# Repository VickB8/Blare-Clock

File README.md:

A Small custom desk clock powered by a XIAO ESP32-C3 with a color display and Wi-Fi time sync.

# Inspiration

I wanted to make a small desk clock that was more interesting than a normal digital clock I decided to design the PCB, Case and firmware myself use an ESP32-C3 so the clock could connect to Wifi and automatically keep the synchronisation.
I also wanted the final clock to look like an actual finished product instead of just a developement board connected to a display.

# How it Works

The clock uses a Seeed Studio XIAO ESP32-C3 as the main microcontroller. When it starts up, it connects to Wi-Fi and gets the current time using NTP.

The time is then displayed on the display.

The electronics are mounted inside a custom 3D-printed case that I designed specifically for the PCB and display.

# Challenges

One of the biggest challenges was getting the display and XIAO ESP32-C3 working together. I had to figure out the correct pins and how to control the display.

I also had some problems with the KiCad libraries and footprints for the XIAO ESP32-C3. Getting the PCB and its 3D models to show correctly took some troubleshooting.

Another challenge was designing the case. I originally made the display opening too small and didn't leave enough room for the display wires and USB connection. I had to go back and modify the case so the display could actually be connected and the USB port could be accessed.

# What I Learned

How to design a PCB in KiCad
How to work with custom footprints and libraries
How to use an ESP32-C3 with Wi-Fi
How NTP time synchronization works
How to design a 3D-printed enclosure around electronics
How to troubleshoot PCB and 3D-model issues

# Components 

Seeed Studio XIAO ESP32-C3
TFT display
Custom PCB
Connecting wires
3D-printed enclosure
MX style keyboard switches
white blank dsa caps
3.3v piezo buzzer
M3x5x4 heat inserts M3x8mm screws

# Software

Arduino IDE
ESP32 Arduino Core
Adafruit GFX Library
Adafruit ST7789 Library
SPI
WiFi
Time / NTP

# Features

Wi-Fi time synchronization
NTP-based accurate time
Color display

# Design Files

PCB

The PCB was designed in KiCad and contains the connections between the XIAO ESP32-C3 and the display.

Schematic

Case

The enclosure was designed to hold the electronics while leaving access for the display and USB port.

Firmware

The firmware is written in Arduino/C++ and handles Wi-Fi connection, NTP time synchronization, and drawing the clock interface on the display.

Final Result

This project helped me learn more about PCB design, embedded programming, displays, and designing physical enclosures for electronics. I started with the individual components and gradually worked toward making the complete clock.

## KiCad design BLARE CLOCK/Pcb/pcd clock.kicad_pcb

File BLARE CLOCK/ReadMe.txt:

# BLARE Clock

A custom digital clock built using a **Seeed Studio XIAO ESP32-C3**, **ST7789 TFT display**, custom PCB, and a 3D-printed enclosure.

## Project Overview

This project is a compact Wi-Fi-enabled digital clock. The ESP32-C3 connects to Wi-Fi and retrieves the current time using an NTP time server. The time and date are displayed on an ST7789 TFT screen.

## Features

* Wi-Fi connectivity
* Automatic time synchronization using NTP
* Digital time display
* Date display
* Custom PCB
* Custom 3D-printed enclosure
* ST7789 TFT display
* Seeed Studio XIAO ESP32-C3

## Hardware

| Component       | Description                |
| --------------- | -------------------------- |
| Microcontroller | Seeed Studio XIAO ESP32-C3 |
| Display         | ST7789 284 × 76 TFT        |
| PCB             | Custom-designed PCB        |
| Enclosure       | Custom 3D-printed case     |
| Firmware        | Arduino / ESP32            |
| Connectivity    | Wi-Fi                      |

## Firmware

The firmware is written using the Arduino IDE and runs on the XIAO ESP32-C3.

The firmware:

1. Initializes the ST7789 display.
2. Connects to Wi-Fi.
3. Synchronizes the clock using an NTP server.
4. Retrieves the local date and time.
5. Displays the time and date on the TFT.

### Libraries

* Adafruit GFX Library
* Adafruit ST7735 and ST7789 Library
* SPI
* WiFi
* ESP32 time functions

## Bill of Materials

| Component                   |                  Quantity |
| --------------------------- | ------------------------: |
| Seeed Studio XIAO ESP32-C3  |                         1 |
| ST7789 284 × 76 TFT Display |                         1 |
| Custom PCB                  |                         1 |
| 3D-printed enclosure        |                         1 |
| Other electronic components | As specified in schematic |

## Project Structure

```text
BLARE-Clock/
├── CAD/
│   └── Clock.step
│
├── PCB/
│   ├── clock.kicad_pro
│   ├── clock.kicad_sch
│   └── clock.kicad_pcb
│
├── Firmware/
│   └── clock.ino
│
├── Production/
│   ├── gerbers.zip
│   ├── Top.step
│   ├── Bottom.step
│
└── README.txt
```

## Tools Used

* KiCad — schematic and PCB design
* Arduino IDE — firmware development
* Blender / CAD software — enclosure design
* 3D printer — enclosure manufacturing

## Credits

This project was created as part of the **Hack Club BLARE** hardware project.

Built with:

* Seeed Studio XIAO ESP32-C3
* ST7789 TFT
* KiCad
* Arduino
* 3D printing

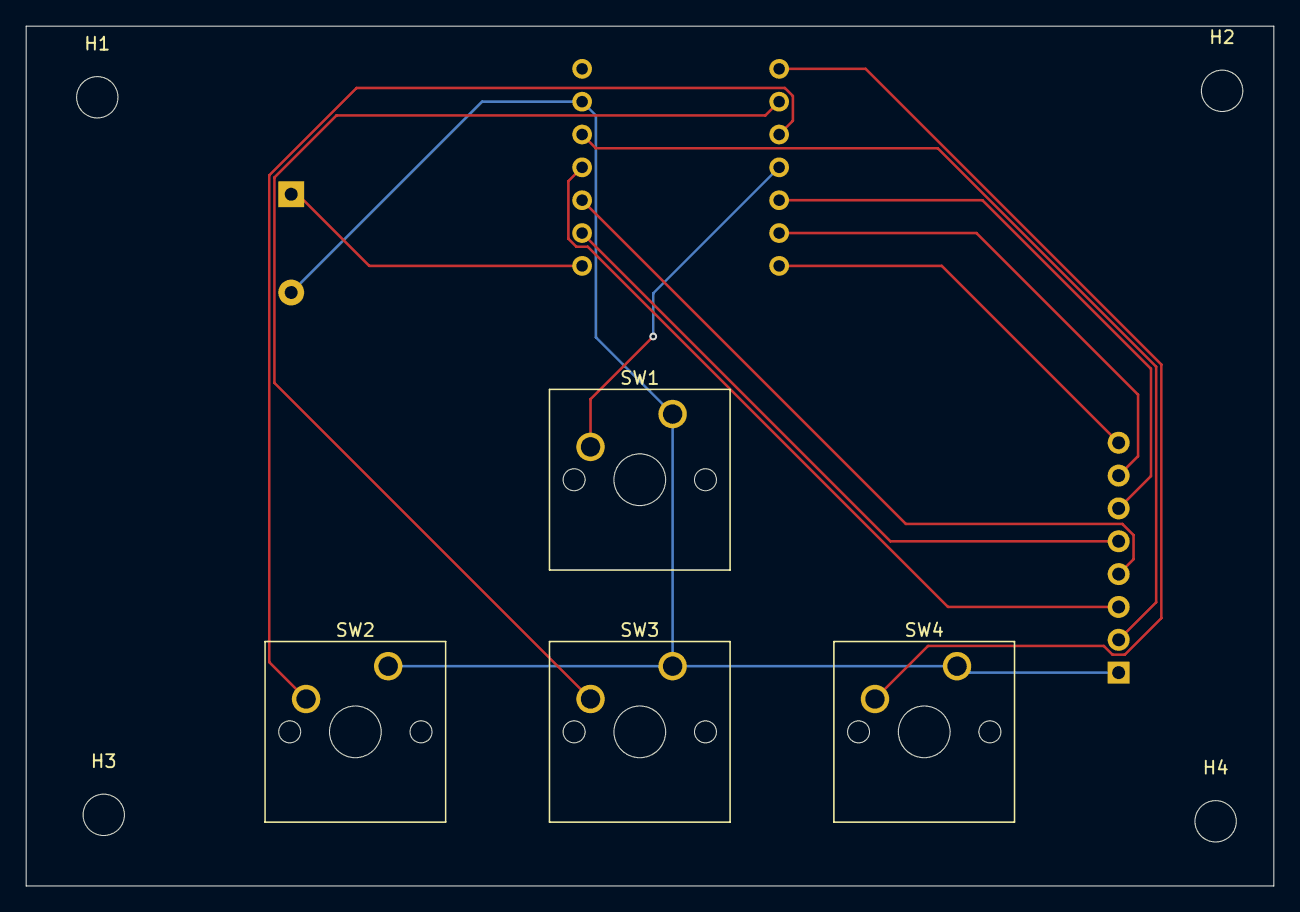
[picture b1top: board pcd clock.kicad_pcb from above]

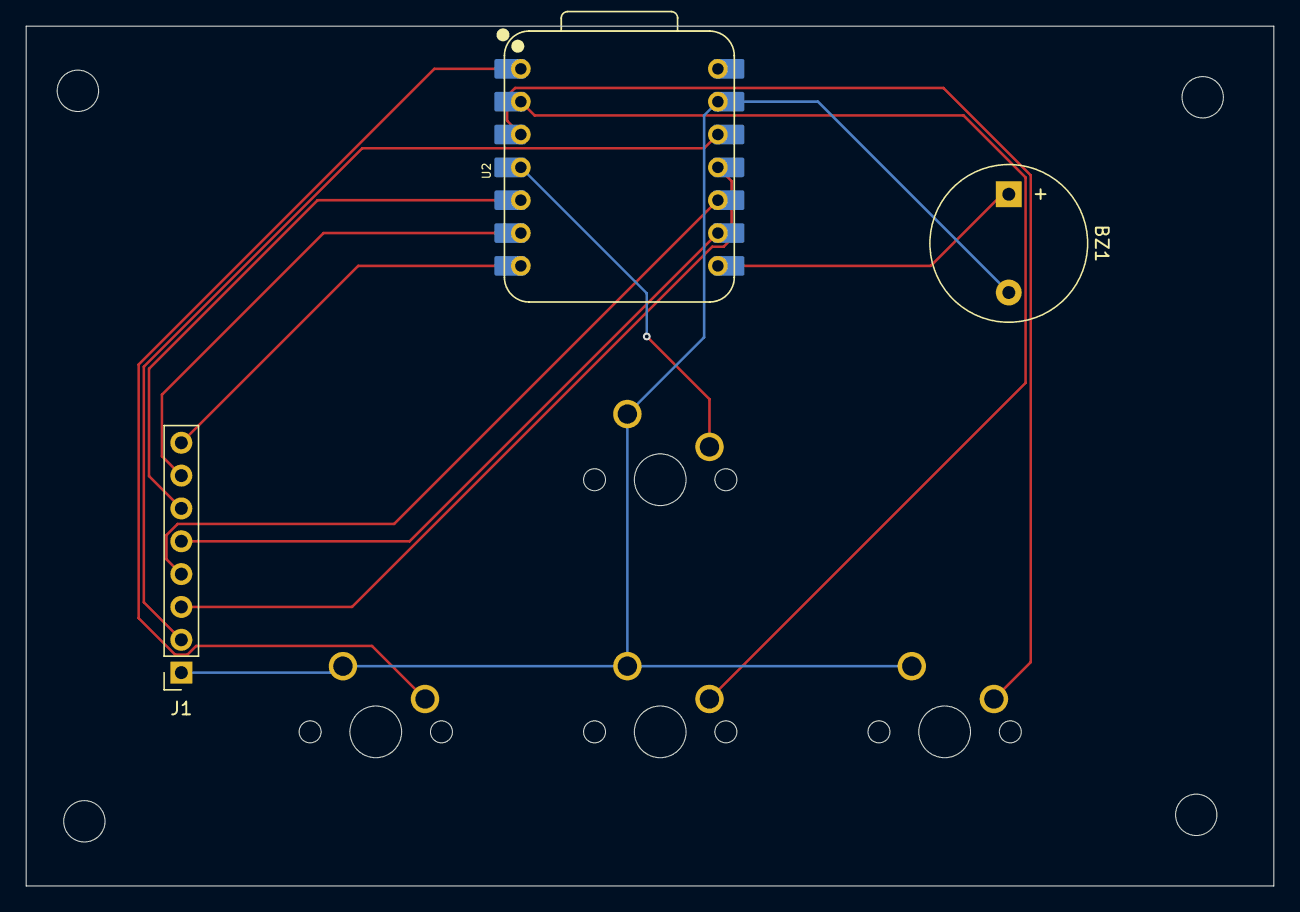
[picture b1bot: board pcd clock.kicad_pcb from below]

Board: 2 copper layers, 96.5 x 66.5 mm, 11 parts (3 on the bottom side), 13 nets.

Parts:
BZ1: Buzzer; Buzzer_12x9.5RM7.6
H1, H2, H3, H4: MountingHole; MountingHole_3.2mm_M3
J1: Conn_01x08_Pin; PinSocket_1x08_P2.54mm_Vertical
SW1, SW2, SW3, SW4: SW_Push; SW_Cherry_MX_1.00u_PCB
U2: XIAO-ESP32-C3-SMD; XIAO-ESP32-C3-DIP

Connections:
+3V3: J1.2, U2.12 (3V3_OUT)
/BL: J1.8, U2.7 (D6)
/CS: J1.7, U2.6 (D5)
/DC: J1.6, U2.5 (D4)
/RST: J1.5, U2.9 (D8)
/SCL: J1.4, U2.10 (D9/BOOT)
/SDA: J1.3, U2.11 (D10)
GND: BZ1.2 (-), J1.1, SW1.1, SW2.1, SW3.1, SW4.1, U2.13 (GND)
unnamed: BZ1.1 (+), U2.8 (D7)
unnamed: SW4.2, U2.1 (D0)
unnamed: SW3.2, U2.2 (D1)
unnamed: SW2.2, U2.3 (D2)
unnamed: SW1.2, U2.4 (D3)
